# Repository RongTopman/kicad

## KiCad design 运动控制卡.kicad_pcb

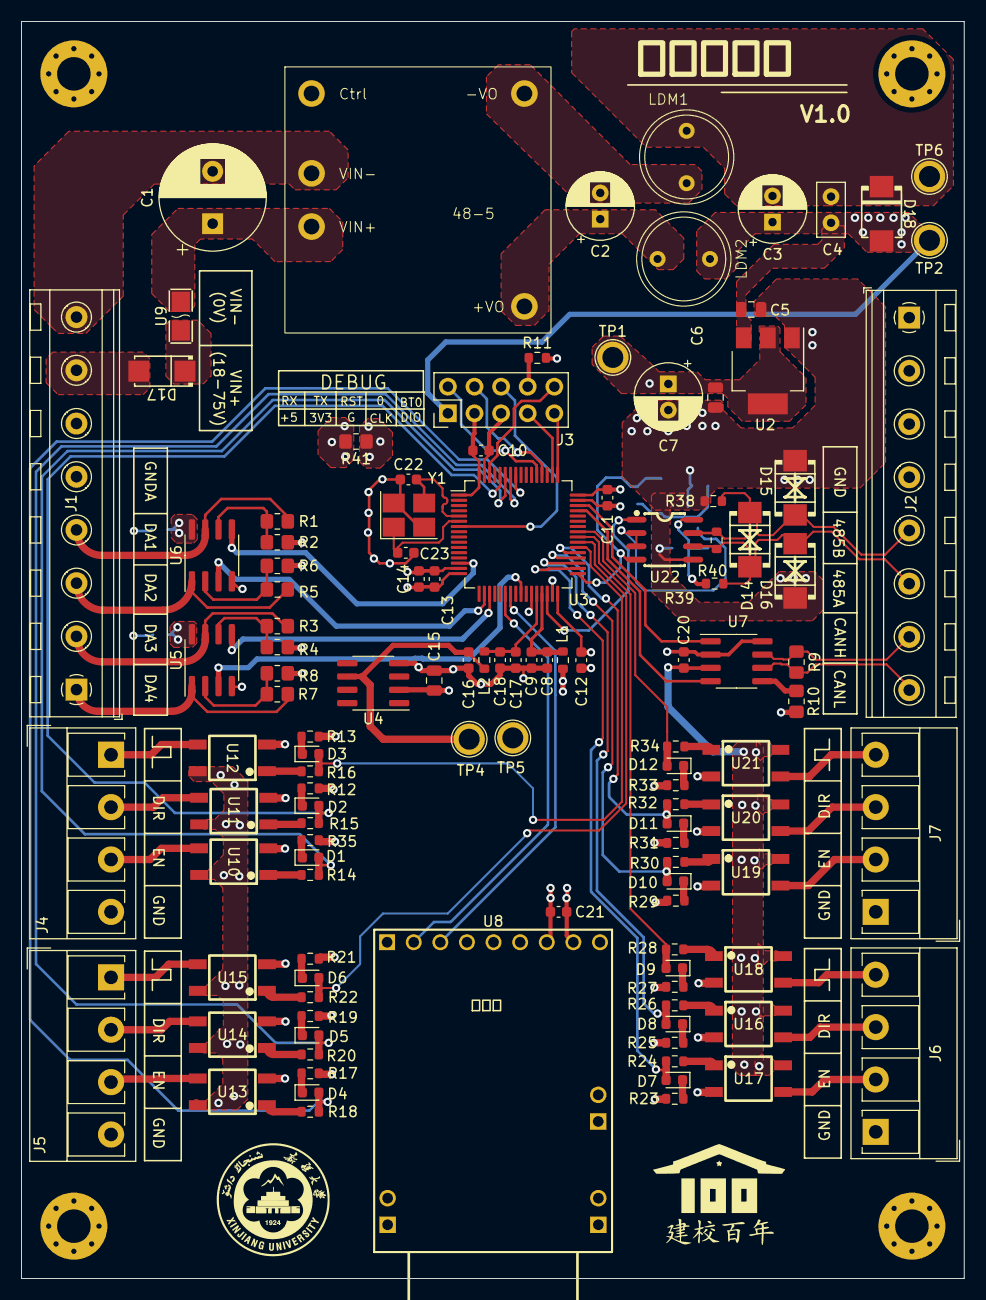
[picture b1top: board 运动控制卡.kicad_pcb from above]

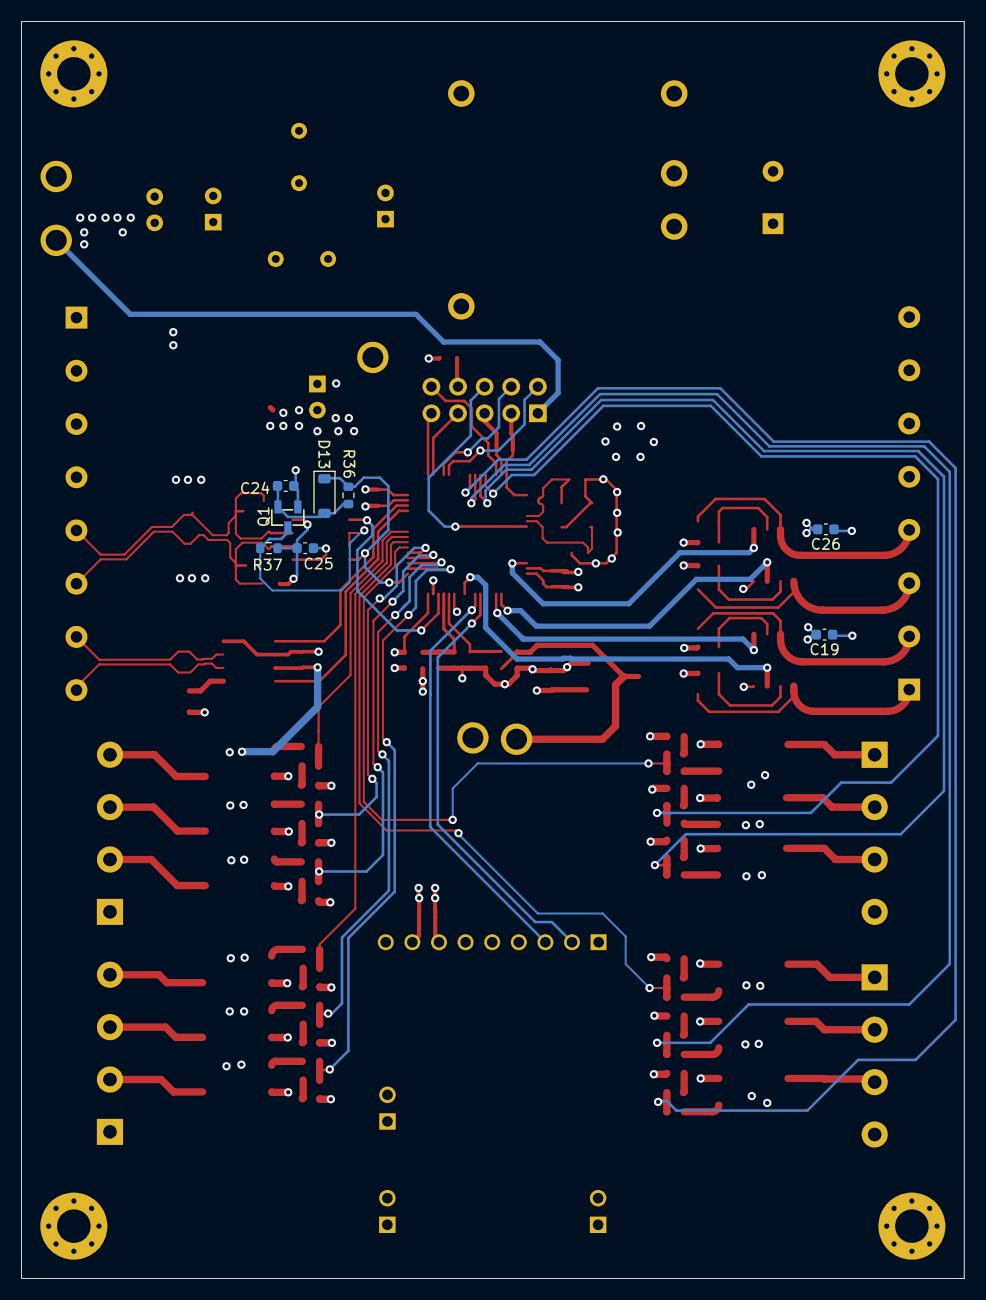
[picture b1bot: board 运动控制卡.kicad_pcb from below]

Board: 4 copper layers, 90.0 x 120.0 mm, 129 parts (8 on the bottom side), 95 nets.

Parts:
C1: 100uF_100V; CP_Radial_D10.0mm_P5.00mm
C2, C3, C7: 220uF_10V; CP_Radial_D6.3mm_P2.50mm
C4: 104_Ceramic; C_Disc_D5.0mm_W2.5mm_P2.50mm
C5, C6, C15: 104; C_0805_2012Metric
C8, C10, C11, C12, C13, C16, C17, C19, C20, C21, C22, C23, C25, C26: 104; C_0603_1608Metric
C9: IUF; C_0603_1608Metric
C14: 4.7UF; C_0603_1608Metric
C18: 1uf; C_0603_1608Metric
C24: 102; C_0603_1608Metric
D1, D2, D3, D4, D5, D6, D7, D8, D9, D10, D11, D12: LED; LED_0603_1608Metric
D13: MBR0520; D_SOD-123
D14, D15, D16: SMB_L4.6-W3.6-LS5.3-BI
D17: SS54 60V/5A; MY
D18: 5V; SMB_L4.3-W3.6-LS5.4-RD
H1, H2, H3, H4: MountingHole_Pad; MountingHole_3.2mm_M3_Pad_Via
J1, J2: Screw_Terminal_01x08; TerminalBlock_RND_205-00238_1x08_P5.08mm_Horizontal
J3: Conn_02x05_Counter_Clockwise; PinHeader_2x05_P2.54mm_Vertical
J4, J5, J6, J7: Screw_Terminal_01x04; TerminalBlock_RND_205-00278_1x04_P5.00mm_Vertical
L1, L2: 600 R@100MHz; R_0603_1608Metric
LDM1, LDM2: 1uH; 工字功率电感_1
Q1: S8050; SOT-23-3_L2.9-W1.3-P1.90-LS2.4-BR
R1, R2, R3, R4, R5, R6, R7, R8: 1K; R_0805_2012Metric_Pad1.20x1.40mm_HandSolder
R9: 120R; R_0805_2012Metric_Pad1.20x1.40mm_HandSolder
R10: 510R; R_0805_2012Metric_Pad1.20x1.40mm_HandSolder
R11, R37: 10K; R_0603_1608Metric
R12, R13, R17, R19, R21, R23, R25, R27, R29, R31, R33, R35: 500R; R_0603_1608Metric
R14, R15, R16, R18, R20, R22, R24, R26, R28, R30, R32, R34, R38, R39: 360R; R_0603_1608Metric
R36: 20K; R_0603_1608Metric
R40: 120R; R_0603_1608Metric
R41: 0R; R_0805_2012Metric_Pad1.20x1.40mm_HandSolder
TP1: 3V3; TestPoint_Plated_Hole_D2.0mm
TP2: 5V; TestPoint_Plated_Hole_D2.0mm
TP4: 2.5V; TestPoint_Plated_Hole_D2.0mm
TP5: GNDA; TestPoint_Plated_Hole_D2.0mm
TP6: GND; TestPoint_Plated_Hole_D2.0mm
U1: 48V-5V; URB4805YMD-10WR3
U2: SOT-223
U3: STM32G474RETx; LQFP-64_10x10mm_P0.5mm
U4: 2.5V; SOIC-8_3.9x4.9mm_P1.27mm
U5, U6: LM358; SOIC-8_3.9x4.9mm_P1.27mm
U7: TJA1051T-3; SOIC-8_3.9x4.9mm_P1.27mm
U8: ZQWL-GE145S/ZQWL-GE145S; ZQWL-GE145S_ZQWL-GE105S
U9: 48V/3A; FUSE-SMD_L3.2-W1.6
U10, U11, U12, U13, U14, U15, U16, U17, U18, U19, U20, U21: OPTO-SMD-4_L4.4-W4.1-P2.54-LS7.0-TL
U22: SOIC-8_L5.0-W4.0-P1.27-LS6.0-BL
Y1: 24M; Crystal_SMD_3225-4Pin_3.2x2.5mm_HandSoldering

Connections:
+3V3: C6.1, C7.1, C10.1, C11.1, C12.1, C13.1, C14.1, C21.2, C25.1, J3.3, L1.1, R10.2, R37.1, R39.1, TP1.1, U2.2 (VOUT), U2.4 (VOUT), U3.1 (VBAT), U3.16 (VDD), U3.32 (VDD), U3.48 (VDD), U3.64 (VDD), U8.8 (3.3V), U22.8 (VCC)
+5V: C3.1, C4.1, C5.1, C15.1, C19.2, C20.1, C26.2, D18.2 (A), J3.1, LDM2.2, TP2.1, U2.3 (VIN), U4.2 (VIN), U5.8 (VCC), U6.8 (VCC), U7.3 (VCC), U10.4 (COL), U11.4 (COL), U12.4 (COL), U13.4 (COL), U14.4 (COL), U15.4 (COL), U16.4 (COL), U17.4 (COL), U18.4 (COL), U19.4 (COL), U20.4 (COL), U21.4 (COL)
/MCU核心/CAN_RX: U3.45 (PA11), U7.4 (RXD)
/MCU核心/CAN_TX: U3.46 (PA12), U7.1 (TXD)
/MCU核心/DAC_OU1: U3.25 (PB1), U5.3 (1IN+)
/MCU核心/DAC_OUT2: U3.19 (PA5), U5.5 (2IN+)
/MCU核心/DAC_OUT3: U3.18 (PA4), U6.3 (1IN+)
/MCU核心/DAC_OUT4: U3.14 (PA2), U6.5 (2IN+)
/MCU核心/DIR1: D2.2 (A), R15.1, U3.60 (PB7)
/MCU核心/DIR2: D5.2 (A), R20.1, U3.58 (PB5)
/MCU核心/DIR3: D8.2 (A), R26.1, U3.35 (PB13)
/MCU核心/DIR4: D11.2 (A), R32.1, U3.37 (PB15)
/MCU核心/EN1: D1.2 (A), R14.1, U3.59 (PB6)
/MCU核心/EN2: D4.2 (A), R18.1, U3.57 (PB4)
/MCU核心/EN3: D7.2 (A), R24.1, U3.34 (PB12)
/MCU核心/EN4: D10.2 (A), R30.1, U3.36 (PB14)
/MCU核心/PWM1: D3.2 (A), R16.1, U3.38 (PC6)
/MCU核心/PWM2: D6.2 (A), R22.1, U3.39 (PC7)
/MCU核心/PWM3: D9.2 (A), R28.1, U3.40 (PC8)
/MCU核心/PWM4: D12.2 (A), R34.1, U3.41 (PC9)
/MCU核心/RS485_RX: D13.1 (K), R36.2, U3.33 (PB11), U22.4 (D)
/MCU核心/RS485_TX: U3.30 (PB10), U22.1 (R)
/MCU核心/USART_RX: U3.23 (PC5), U8.3 (RXD)
/MCU核心/USART_TX: U3.22 (PC4), U8.2 (TXD)
/MCU核心/VREF+: C16.2, L2.1, TP4.1, U4.6 (VOUT)
/RS485/485+: D14.1 (K), D16.1 (K), J2.6, R39.2, R40.1, U22.6 (A/Y)
/RS485/485-: D14.2 (A), D15.2 (A), J2.5, R38.1, R40.2, U22.7 (B/Z)
/can总线/CAN+: J2.7, R9.2, U7.7 (CANH)
/can总线/CAN-: J2.8, R9.1, U7.6 (CANL)
/steper/ST_DIR1: J4.2, U11.3 (EM)
/steper/ST_DIR2: J5.2, U14.3 (EM)
/steper/ST_DIR3: J6.3, U17.3 (EM)
/steper/ST_DIR4: J7.3, U20.3 (EM)
/steper/ST_EN1: J4.3, U10.3 (EM)
/steper/ST_EN2: J5.3, U13.3 (EM)
/steper/ST_EN3: J6.2, U16.3 (EM)
/steper/ST_EN4: J7.2, U19.3 (EM)
/steper/ST_PWM1: J4.1, U12.3 (EM)
/steper/ST_PWM2: J5.1, U15.3 (EM)
/steper/ST_PWM3: J6.4, U18.3 (EM)
/steper/ST_PWM4: J7.4, U21.3 (EM)
/接口/DAC_1: J1.1, R7.2, U5.1 (1OUT)
/接口/DAC_2: J1.2, R3.2, U5.7 (2OUT)
/接口/DAC_3: J1.3, R5.2, U6.1 (1OUT)
/接口/DAC_4: J1.4, R1.2, U6.7 (2OUT)
/接口/VIN+: D17.2 (A), J1.7
/接口/VIN-: C1.2, J1.8, U1.2 (VIN-)
/电源/VIN: C1.1, U1.3 (VIN+), U9.2
BOOT0: J3.10, U3.62 (PB9)
GND: C3.2, C4.2, C5.2, C6.2, C7.2, C10.2, C11.2, C12.2, C13.2, C14.2, C20.2, C21.1, C22.1, C23.2, C24.1, C25.2, D15.1 (K), D16.2 (A), D18.1 (K), J3.5, J4.4, J5.4, J6.1, J7.1, LDM1.2, Q1.1 (E), R11.2, R12.2, R13.2, R17.2, R19.2, R21.2, R23.2, R25.2, R27.2, R29.2, R31.2, R33.2, R35.2, R38.2, R41.1, TP6.1, U2.1 (GND), U3.15 (VSS), U3.31 (VSS), U3.47 (VSS), U3.63 (VSS), U7.2 (GND), U7.8 (S), U8.7 (GND), U8.14 (PGND), U8.15 (PGND), U10.2 (CAT), U11.2 (CAT), U12.2 (CAT), U13.2 (CAT), U14.2 (CAT), U15.2 (CAT), U16.2 (CAT), U17.2 (CAT), U18.2 (CAT), U19.2 (CAT), U20.2 (CAT), U21.2 (CAT), U22.5 (GND), Y1.2, Y1.4
GNDA: C8.2, C9.2, C15.2, C16.1, C17.1, C18.1, C19.1, C26.1, J1.5, R2.1, R4.1, R6.1, R8.1, R41.2, TP5.1, U3.27 (VSSA), U4.4 (GND), U5.4 (GND), U6.4 (GND)
unnamed: D1.1 (K), R35.1
unnamed: D2.1 (K), R12.1
unnamed: D3.1 (K), R13.1
unnamed: D4.1 (K), R17.1
unnamed: D5.1 (K), R19.1
unnamed: D6.1 (K), R21.1
unnamed: D7.1 (K), R23.1
unnamed: D8.1 (K), R25.1
unnamed: D9.1 (K), R27.1
unnamed: D10.1 (K), R29.1
unnamed: D11.1 (K), R31.1
unnamed: D12.1 (K), R33.1
unnamed: C24.2, D13.2 (A), Q1.2 (B), R36.1
unnamed: D17.1 (K), U9.1
unnamed: J3.8, R11.1
unnamed: Q1.3 (C), R37.2, U22.2 (RE), U22.3 (DE)
unnamed: C2.1, LDM2.1, U1.4 (+VO)
unnamed: C2.2, LDM1.1, U1.5 (-VO)
unnamed: C22.2, U3.5 (PF0), Y1.3
unnamed: C23.1, U3.6 (PF1), Y1.1
unnamed: C17.2, C18.2, L2.2, U3.28 (VREF+)
unnamed: R7.1, R8.2, U5.2 (1IN-)
unnamed: R3.1, R4.2, U5.6 (2IN-)
unnamed: R5.1, R6.2, U6.2 (1IN-)
unnamed: R1.1, R2.2, U6.6 (2IN-)
unnamed: R10.1, U7.5 (VIO)
unnamed: R14.2, U10.1 (AN)
unnamed: R15.2, U11.1 (AN)
unnamed: R16.2, U12.1 (AN)
unnamed: R18.2, U13.1 (AN)
unnamed: R20.2, U14.1 (AN)
unnamed: R22.2, U15.1 (AN)
unnamed: R24.2, U16.1 (AN)
unnamed: R26.2, U17.1 (AN)
unnamed: R28.2, U18.1 (AN)
unnamed: R30.2, U19.1 (AN)
unnamed: R32.2, U20.1 (AN)
unnamed: R34.2, U21.1 (AN)
RST: J3.6, U3.7 (PG10)
SWCLK: J3.7, U3.50 (PA14)
SWDIO: J3.9, U3.49 (PA13)
UART4_RX: J3.2, U3.53 (PC11)
UART4_TX: J3.4, U3.52 (PC10)
VDDA: C8.1, C9.1, L1.2, U3.29 (VDDA)

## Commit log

2024-02-20 开仓大吉
2024-02-21 git test
